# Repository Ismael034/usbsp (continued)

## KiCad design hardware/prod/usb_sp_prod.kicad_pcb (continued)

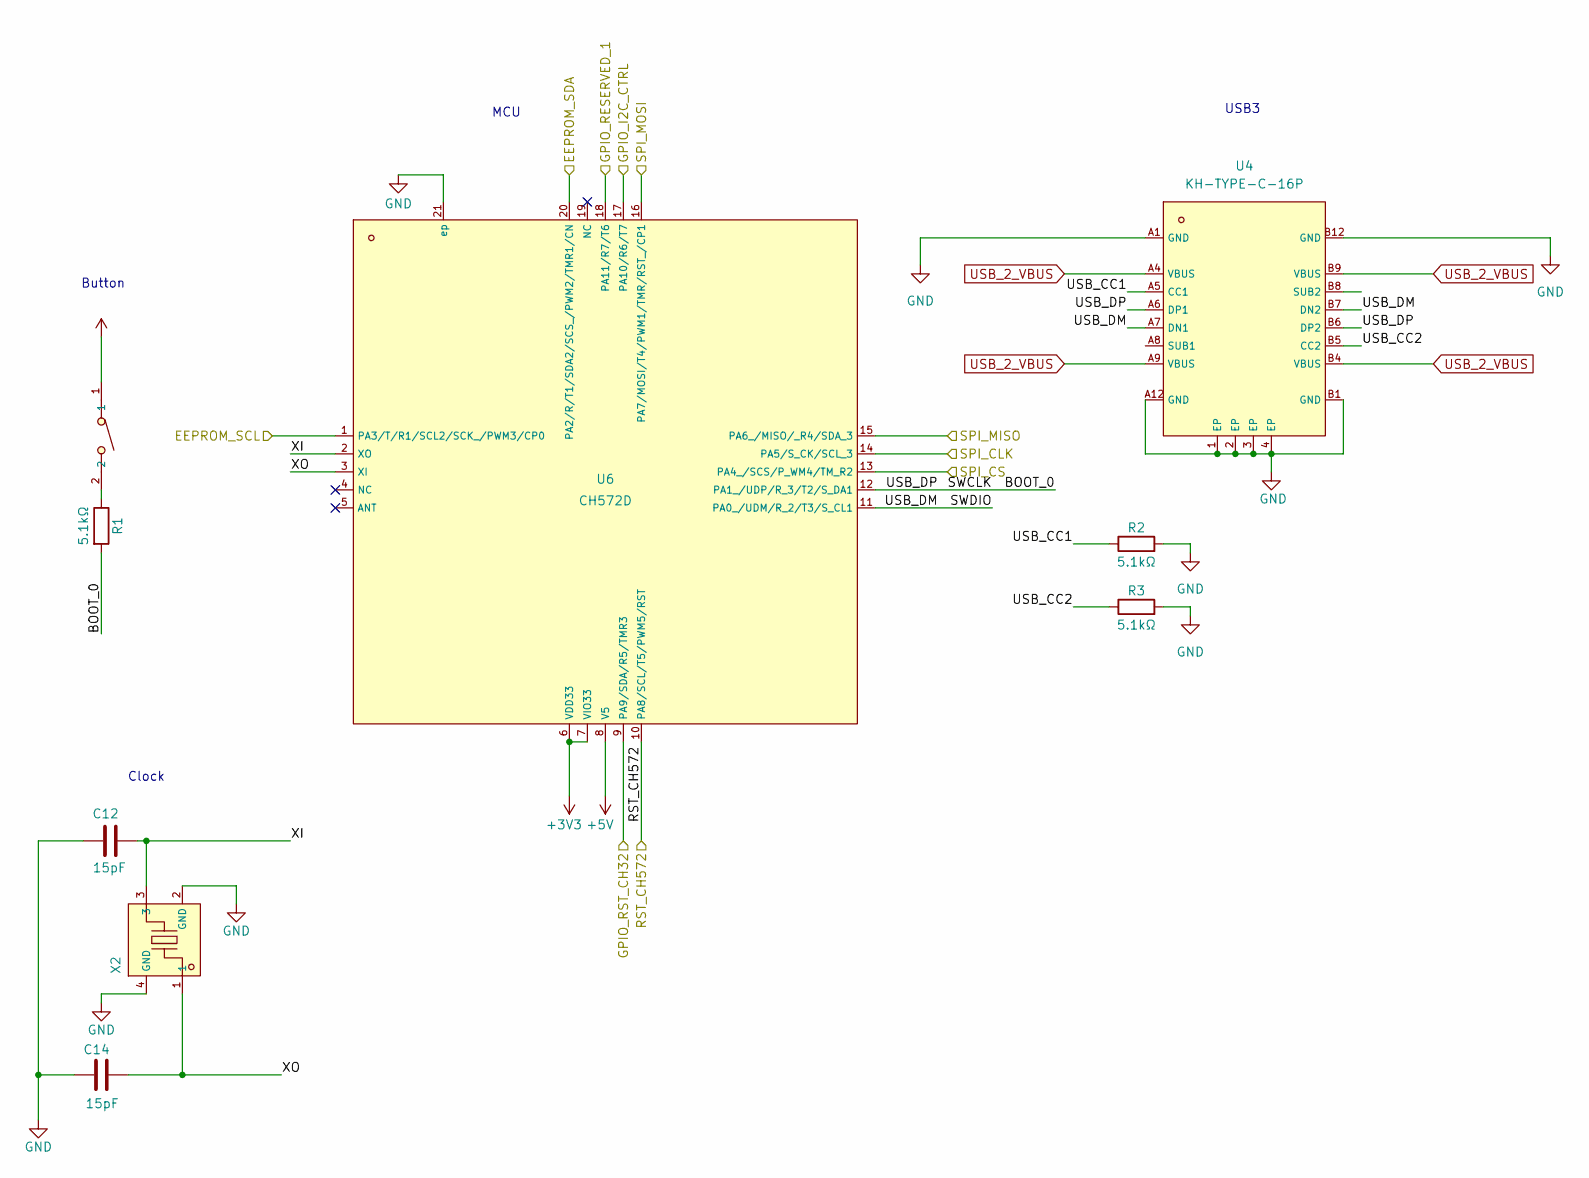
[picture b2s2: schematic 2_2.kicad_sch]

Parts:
BOOT_1: SW-SMD_L3.9-W3.0-P4.45; Manufacturer Part TS-1088-AR02016; LCSC Part Name 4*3*2mm 立贴 轻触开关
C12, C14: 15pF; C_0402_1005Metric; Manufacturer Part 0402CG150J500NT; LCSC Part Name 15pF ±5% 50V
R1, R2, R3: 5.1kΩ; R_0402_1005Metric
U4: KH-TYPE-C-16P; USB-C-SMD_KH-TYPE-C-16P; LCSC C709357
U6: CH572D; QFN-20_L3.0-W3.0-P0.40-TL-EP1.7; LCSC C46597863
X2: XTM20032000DT00351001; CRYSTAL-SMD_4P-L2.0-W1.6-BL; LCSC C37635331

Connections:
+3V3: BOOT_1.1, U6.6 (VDD33), U6.7 (VIO33); also elsewhere on the board
+5V: U6.8 (V5)
/CH32V203/EEPROM_SCL: U6.1 (PA3/T/R1/SCL2/SCK_/PWM3/CP0); also elsewhere on the board
/CH32V203/EEPROM_SDA: U6.20 (PA2/R/T1/SDA2/SCS_/PWM2/TMR1/CN); also elsewhere on the board
/CH32V203/GPIO_I2C_CTRL: U6.17 (PA10/R6/T7); also elsewhere on the board
/CH32V203/GPIO_RESERVED_1: U6.18 (PA11/R7/T6); also elsewhere on the board
/CH32V203/GPIO_RST_CH32: U6.9 (PA9/SDA/R5/TMR3); also elsewhere on the board
/CH32V203/RST: U6.10 (PA8/SCL/T5/PWM5/RST); also elsewhere on the board
/CH32V203/SPI_CLK: U6.14 (PA5/S_CK/SCL_3); also elsewhere on the board
/CH32V203/SPI_CS: U6.13 (PA4_/SCS/P_WM4/TM_R2); also elsewhere on the board
/CH32V203/SPI_MISO: U6.15 (PA6_/MISO/_R4/SDA_3); also elsewhere on the board
/CH32V203/SPI_MOSI: U6.16 (PA7/MOSI/T4/PWM1/TMR/RST_/CP1); also elsewhere on the board
/CH572D/BOOT_0: R1.2, U4.A6 (DP1), U4.B6 (DP2), U6.12 (PA1_/UDP/R_3/T2/S_DA1)
/CH572D/SWDIO: U4.A7 (DN1), U4.B7 (DN2), U6.11 (PA0_/UDM/R_2/T3/S_CL1)
/CH572D/USB_CC1: R2.1, U4.A5 (CC1)
/CH572D/USB_CC2: R3.1, U4.B5 (CC2)
/CH572D/XI: C12.1, U6.2 (XO), X2.3
/CH572D/XO: C14.2, U6.3 (XI), X2.1
GND: C12.2, C14.1, R2.2, R3.2, U4.1 (EP), U4.2 (EP), U4.3 (EP), U4.4 (EP), U4.A1 (GND), U4.A12 (GND), U4.B1 (GND), U4.B12 (GND), U6.21 (ep), X2.2 (GND), X2.4 (GND); also elsewhere on the board
unnamed: BOOT_1.2, R1.1
USB_2_VBUS: U4.A4 (VBUS), U4.A9 (VBUS), U4.B4 (VBUS), U4.B9 (VBUS); also elsewhere on the board

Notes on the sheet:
USB3
Button
MCU
Clock

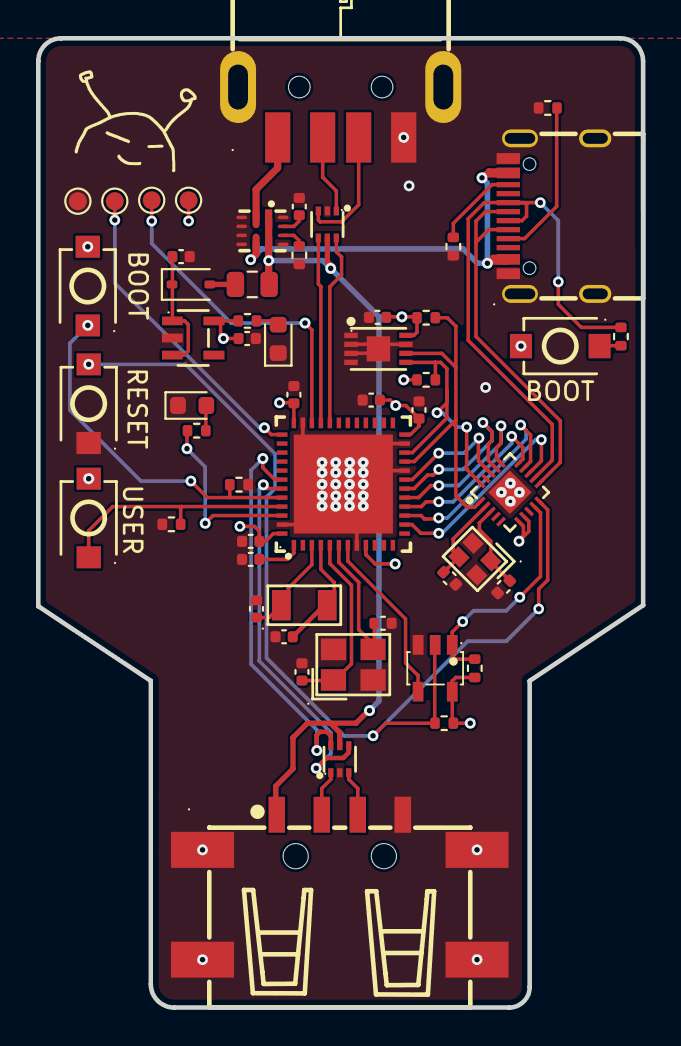
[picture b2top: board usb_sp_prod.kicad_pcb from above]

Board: 4 copper layers, 33.6 x 53.9 mm, 53 parts (0 on the bottom side), 47 nets.

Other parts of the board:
TP1, TP2, TP3, TP4: TestPoint; TestPoint_Pad_D1.0mm

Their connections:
+3V3: TP3.1 (1_1); also elsewhere on the board
/CH32V203/SWCLK: TP1.1 (1_1); also elsewhere on the board
/CH32V203/SWDIO: TP2.1 (1_1); also elsewhere on the board
GND: TP4.1 (1_1); also elsewhere on the board

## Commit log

2025-09-13 add: Initial hardware prototype
2025-09-13 refactor: minor schematic visual changes
2025-09-15 add: Toolchain and test firmware for ch32v203
2025-09-15 chore: remove .vscode folder
2025-09-16 docs: update README.md
2025-09-17 add: include main file for the main firmware, minor doc and style fixes
2025-09-18 fix: add missing cs line to spi bus
2025-09-18 style: improve trace paths
2025-09-18 fix: spi cs trace clearance
2025-09-18 chore: update pdf schematic
2025-10-21 ch32v203: usb relay queue implementation
2025-10-21 test commit
2026-02-15 add developemnt board and fix issue related to dual i2c access
2026-02-15 hardware: add developemnt board and fix issue related to dual i2c access
2026-02-15 website: initial support for webusb
2026-02-15 c572d: initial firmware with webusb support and eeprom read and write functionality
2026-03-03 feat: tlv implementation for eeprom write and read functionality
2026-03-04 hardware: update KiCad design files
2026-03-04 format (ch572d): remove unused locals to remove warnigns at compilation time
2026-03-04 feat: (utils): add helper tool to test 24c02 eeprom
2026-03-04 chore (ch32v203): fix meson.build build process
2026-03-04 chore (ch572d): fix meson.build build process
2026-03-04 chore: fix meson.build build process
2026-03-04 feat (ch572): add microtlv as external library
2026-03-04 fix (ch32v203): minor usb drive improvements and style changes
2026-03-05 fix (ch32v203): eeprom tlv implementation, replaces old raw implementation
2026-03-05 style (ch32v203): code refactoring and style improvements
2026-03-05 feat (ch32v203): migrate usb identifiers write user action to tlv implementation
2026-03-05 refactor (ch32v203): refactor usb relay queue by creating new helper functions
2026-03-05 fix (ch32v203): rework usb relay control-path in relay.c/relay.h by replacing descriptor-specific handlers with generic setup/nodata, new polling functionality and local descriptor relay
2026-03-05 refactor (ch32v203): disable detailed logging
2026-03-05 refactor (ch32v203): add reset cause, adapt implementation to new relay and queue changes
2026-03-05 chore (ch572d): add build dependencies
2026-03-05 refactor (ch572d): remove build warning by setting the unused attribute
2026-03-05 fix (website): improve tlv implementation
2026-03-05 refactor (ch572d): remove dead code
2026-03-05 chore: new paths to gitignore
2026-03-05 refactor (ch572d): update riscv core
2026-03-07 refactor (ch32v203): improve usart output for test firmware
2026-03-07 refactor (ch32v203): migrate only needed test resources to test firmware folder
2026-03-07 chore (ch32v203): upgrade mounriver studio project files
2026-03-07 feat (hardware): create production kicad project
2026-03-07 chore (ch32v203): normalize usart logs
2026-03-07 fix (ch32v203): increase max ep numbers to 8
2026-03-07 refactor (ch32v203): remove unnecessary functions previously only used for the test firmware
2026-03-07 fix (ch32v203): increase ep max pma buffer size to 64 bytes
2026-04-13 refactor(website): extract app state and WebUSB hooks
2026-04-13 feat(website): improve USB settings and debug tools
2026-04-13 feat(website): add HID mouse decoding and trace export
2026-04-13 chore(website): add branding and container assets
2026-04-13 feat(ch32v203): add SPI bridge and capture support
2026-04-13 chore(ch32v203): normalize WCH project flash target path
2026-04-13 feat(ch572d): add SPI master bridge and EEPROM bus control
2026-04-13 feat(ch572d): add WebUSB commands for reset, capture and USB info
2026-04-13 chore(ch572d): update WCH project settings
2026-04-13 chore(website): run docker compose in release mode
2026-04-13 fix(website): guard WebUSB access on unsupported browsers
2026-04-13 chore(website): publish release container on port 80
2026-04-13 feat(hardware): add TPS2121 power mux symbol and footprint assets
2026-04-13 feat(hardware-dev): replace mode transistors with TPS2121 power mux
2026-04-13 feat(hardware-prod): replace mode transistors with TPS2121 power mux
2026-04-13 fix(website): render mouse trace from full capture history
2026-04-13 feat(website): add keyboard text viewer for HID captures
2026-04-13 feat(ch32v203): apply EEPROM USB overrides to active descriptors
2026-04-13 fix(ch32v203): serve patched descriptors from relay control path
2026-04-13 feat(ch32v203): honor EEPROM capture and export settings
2026-04-14 fix(ch32v203): store connected USB values without duplicating descriptors
2026-04-14 fix(website): add connect timeouts and WebUSB step logging
2026-04-14 fix(website): recommend Zadig on Windows WebUSB claim errors
2026-04-16 chore: use USBsp casing
2026-04-17 feat(ch572d): advertise USBsp WebUSB identity
2026-04-17 fix(ch32v203): read USB strings with device LANGID
2026-04-18 fix(usbsp): validate active USB info offsets
2026-04-19 fix(website): improve connection alerts
2026-04-20 fix(usbsp): clear missing imported USB strings
2026-04-20 fix(website): warn when capture packets drop
2026-04-20 fix(ch32v203): reserve full EP0 PMA for mirrored descriptors
2026-04-20 fix(usbsp): remove capture-on-boot setting
2026-04-20 fix(website): auto-detect HID mouse reports
2026-04-20 chore(website): update control panel copy
2026-04-21 fix(ch32v203): reserve PMA for IN endpoints
2026-04-21 fix(website): parse capture packet lengths
2026-04-21 fix(ch572d): fix capture SPI polling
2026-04-21 fix(ch32v203): preserve original capture packet lengths
2026-04-21 fix(website): paginate capture packets and default to raw view
2026-06-07 deploy: 62ccc7dfbc3ea76330a328bd388d90c74ac38240
2026-06-07 deploy: 77e738691e2730d117821ae2fc59ce8a1e031561
2026-06-07 deploy: 4af73e9747e8e49a1f4d48686e25fab5da898b26
2026-06-07 ci(website): add GitHub Pages deploy workflow
2026-06-07 fix(website): use correct GitHub Pages asset paths
2026-06-07 chore(website): deploy built website to gh-pages
2026-06-07 fix(website): correct favicon path on GitHub Pages
2026-06-07 feat(hardware): update board design assets
2026-06-07 fix(website): simplify USB configuration inputs
